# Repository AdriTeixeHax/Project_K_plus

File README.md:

# Project K+
DIY, Modular, Open Source Mechanical Keyboard and Macro-Pad with per-key RGB lighting.

## Features (keep in mind they are all optional or customizable):
- Per-key RGB lighting (because that's all that matters) using WS2812(B) 5050 SMD LEDs.
- RGB compatible mechanical switches.
- Modular design: detachable Macro-Pad, arrow keys, etc. With more room for expansion. Attachable via magnets placed all over the keyboard case.
- USB-C connectors for easy hot-swapping.
- Integrated 4-port USB 2.0 hub, with downstream USB-A and/or USB-C ports. If a USB-C port is connected, a USB-A port will be disconnected (on design process).
-

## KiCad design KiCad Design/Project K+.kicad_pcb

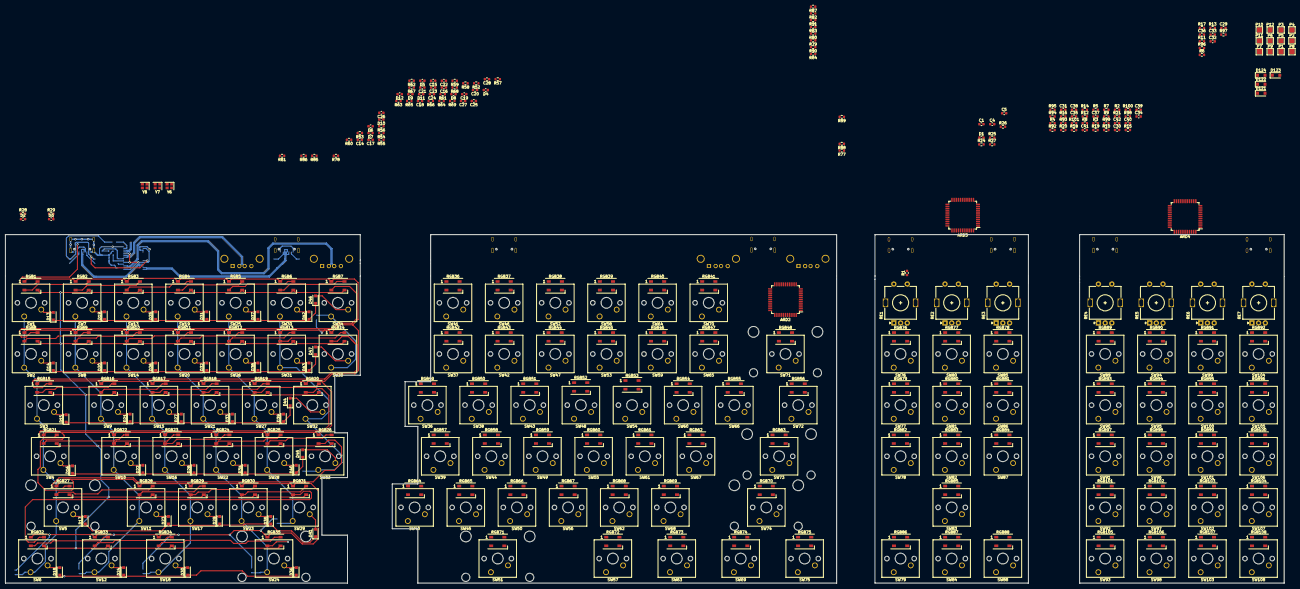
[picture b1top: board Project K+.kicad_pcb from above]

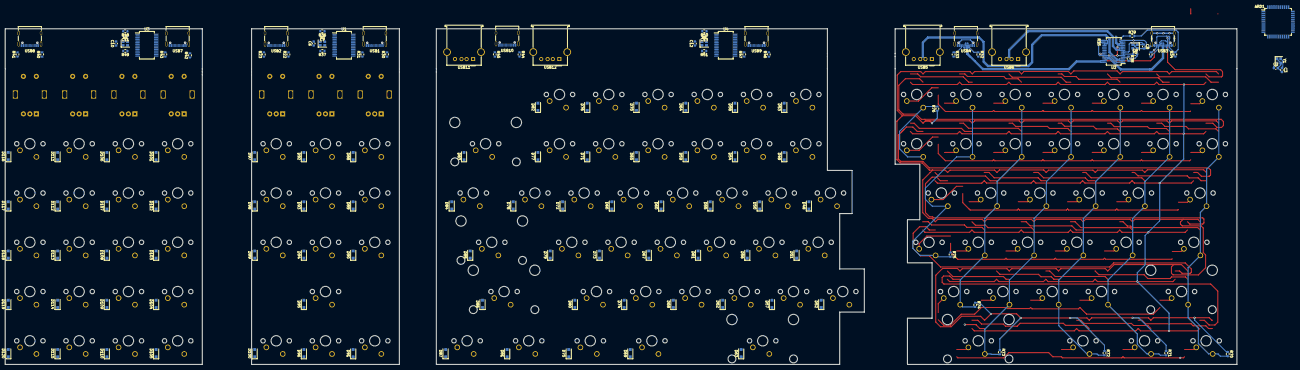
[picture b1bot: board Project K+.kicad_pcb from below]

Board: 2 copper layers, 476.2 x 129.8 mm, 530 parts (136 on the bottom side), 436 nets.

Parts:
ARD1, ARD2, ARD3, ARD4: ATmega32U4-A; TQFP-44_10x10mm_P0.8mm
C1, C5, C20, C21, C22, C23, C27, C28: 1uF; C_0603_1608Metric
C2, C3, C6, C7, C8, C9, C10, C11, C12, C13, C14, C15, C16, C17, C24, C25: 20pF; C_0603_1608Metric
C4, C18, C19, C26: 0.1uF; C_0603_1608Metric
C29, C30, C31, C32, C33, C34, C35, C36, C37, C38, C39, C40, C41, C42: 100n; C_0603_1608Metric
D1, D6, D8, D11: LED; C_0603_1608Metric
D2, D4, D5, D10: G; C_0603_1608Metric
D3, D7, D9, D12: Y; C_0603_1608Metric
D13, D14, D15, D16, D17, D18, D19, D20, D21, D22, D23, D24, D25, D26, D27, D28, D29, D30, D31, D32, D33, D34, D35, D36, D37, D38, D39, D40, D41, D42, D43, D44, D45, D46, D47, D48, D49, D50, D51, D52, D53, D54, D55, D56, D57, D58, D59, D60, D61, D62, D63, D64, D65, D66, D67, D68, D69, D70, D71, D72, D73, D74, D75, D76, D77, D78, D79, D80, D81, D82, D83, D84, D85, D86, D87, D88, D89, D90, D91, D92, D93, D94, D95, D96, D97, D98, D99, D100, D101, D102, D103, D104, D105, D106, D107, D108, D109, D110, D111, D112, D113, D114, D115, D116, D117, D118, D119, D120, D121, D122, D123, D124: D; D_SOD-123F
P1, P2, P3, P4, P5, P6, P7, P8, P9, P10, P11, P12: TESTPAD; TestPoint_Pad_2.0x2.0mm
R1, R10, R95: 220R; R_0603_1608Metric
R2, R3, R4, R5, R6, R7, R8, R9, R11, R12, R13, R14, R15, R16, R17, R18, R19, R20, R21, R25, R56, R57, R66, R70, R71, R72, R73, R74, R75, R76, R77, R78, R79, R80, R81, R82, R83, R84, R85, R86, R87, R88, R89, R90, R91, R92, R93, R94, R96, R97, R98, R99, R100, R101: 10K; R_0603_1608Metric
R22, R23, R32, R33, R40, R41, R44, R45: 5.1K; R_0603_1608Metric
R24, R60, R62, R68: 1K; R_0603_1608Metric
R26, R27, R52, R53, R54, R55, R64, R65: 22R; R_0603_1608Metric
R28, R29, R58, R59, R61, R63, R67, R69: 330R; R_0603_1608Metric
R30, R31, R34, R35, R42, R43, R46, R47: 56K; R_0603_1608Metric
R36, R37, R38, R39, R48, R49, R50, R51: 680R; R_0603_1608Metric
RE1, RE2, RE3, RE4, RE5, RE6, RE7: RotaryEncoder_Alps_EC11E-Switch_Vertical_H20mm
RGB1, RGB2, RGB3, RGB4, RGB5, RGB6, RGB7, RGB8, RGB9, RGB10, RGB11, RGB12, RGB13, RGB14, RGB15, RGB16, RGB17, RGB18, RGB19, RGB20, RGB21, RGB22, RGB23, RGB24, RGB25, RGB26, RGB27, RGB28, RGB29, RGB30, RGB31, RGB32, RGB33, RGB34, RGB35, RGB36, RGB37, RGB38, RGB39, RGB40, RGB41, RGB42, RGB43, RGB44, RGB45, RGB46, RGB47, RGB48, RGB49, RGB50, RGB51, RGB52, RGB53, RGB54, RGB55, RGB56, RGB57, RGB58, RGB59, RGB60, RGB61, RGB62, RGB63, RGB64, RGB65, RGB66, RGB67, RGB68, RGB69, RGB70, RGB71, RGB72, RGB73, RGB74, RGB75, RGB76, RGB77, RGB78, RGB79, RGB80, RGB81, RGB82, RGB83, RGB84, RGB85, RGB86, RGB87, RGB88, RGB89, RGB90, RGB91, RGB92, RGB93, RGB94, RGB95, RGB96, RGB97, RGB98, RGB99, RGB100, RGB101, RGB102, RGB103, RGB104, RGB105, RGB106, RGB107, RGB108: WS2812B; LED_WS2812B_PLCC4_5.0x5.0mm_P3.2mm
SW1: ESC; SW_Cherry_MX_1.00u_PCB
SW2: `; SW_Cherry_MX_1.00u_PCB
SW3: TAB; SW_Cherry_MX_1.50u_PCB
SW4: CAPS; SW_Cherry_MX_1.75u_PCB
SW5: L_SHIFT; SW_Cherry_MX_2.25u_PCB
SW6: L_CTRL; SW_Cherry_MX_1.25u_PCB
SW7: F1; SW_Cherry_MX_1.00u_PCB
SW8: 1; SW_Cherry_MX_1.00u_PCB
SW9: Q; SW_Cherry_MX_1.00u_PCB
SW10: A; SW_Cherry_MX_1.00u_PCB
SW11: Z; SW_Cherry_MX_1.00u_PCB
SW12: OS; SW_Cherry_MX_1.25u_PCB
SW13: F2; SW_Cherry_MX_1.00u_PCB
SW14: 2; SW_Cherry_MX_1.00u_PCB
SW15: W; SW_Cherry_MX_1.00u_PCB
SW16: S; SW_Cherry_MX_1.00u_PCB
SW17: X; SW_Cherry_MX_1.00u_PCB
SW18: L_ALT; SW_Cherry_MX_1.25u_PCB
SW19: F3; SW_Cherry_MX_1.00u_PCB
SW20: 3; SW_Cherry_MX_1.00u_PCB
SW21: E; SW_Cherry_MX_1.00u_PCB
SW22: D; SW_Cherry_MX_1.00u_PCB
SW23: C; SW_Cherry_MX_1.00u_PCB
SW24: L_SPACE; SW_Cherry_MX_2.25u_PCB
SW25: F4; SW_Cherry_MX_1.00u_PCB
SW26: 4; SW_Cherry_MX_1.00u_PCB
SW27: R; SW_Cherry_MX_1.00u_PCB
SW28: F; SW_Cherry_MX_1.00u_PCB
SW29: V; SW_Cherry_MX_1.00u_PCB
SW30: F5; SW_Cherry_MX_1.00u_PCB
SW31: 5; SW_Cherry_MX_1.00u_PCB
SW32: T; SW_Cherry_MX_1.00u_PCB
SW33: G; SW_Cherry_MX_1.00u_PCB
SW34: F6; SW_Cherry_MX_1.00u_PCB
SW35: 6; SW_Cherry_MX_1.00u_PCB
SW36: Y; SW_Cherry_MX_1.00u_PCB
SW37: 7; SW_Cherry_MX_1.00u_PCB
SW38: U; SW_Cherry_MX_1.00u_PCB
SW39: H; SW_Cherry_MX_1.00u_PCB
SW40: B; SW_Cherry_MX_1.00u_PCB
SW41: F7; SW_Cherry_MX_1.00u_PCB
SW42: 8; SW_Cherry_MX_1.00u_PCB
SW43: I; SW_Cherry_MX_1.00u_PCB
SW44: J; SW_Cherry_MX_1.00u_PCB
SW45: N; SW_Cherry_MX_1.00u_PCB
SW46: F8; SW_Cherry_MX_1.00u_PCB
SW47: 9; SW_Cherry_MX_1.00u_PCB
SW48: O; SW_Cherry_MX_1.00u_PCB
SW49: K; SW_Cherry_MX_1.00u_PCB
SW50: M; SW_Cherry_MX_1.00u_PCB
SW51: R_SPACE; SW_Cherry_MX_2.25u_PCB
SW52: F9; SW_Cherry_MX_1.00u_PCB
SW53: 0; SW_Cherry_MX_1.00u_PCB
SW54: P; SW_Cherry_MX_1.00u_PCB
SW55: L; SW_Cherry_MX_1.00u_PCB
SW56: ,; SW_Cherry_MX_1.00u_PCB
SW57: R_ALT; SW_Cherry_MX_1.25u_PCB
SW58: F10; SW_Cherry_MX_1.00u_PCB
SW59: -; SW_Cherry_MX_1.00u_PCB
SW60: [; SW_Cherry_MX_1.00u_PCB
SW61: ;; SW_Cherry_MX_1.00u_PCB
SW62: .; SW_Cherry_MX_1.00u_PCB
SW63: FN; SW_Cherry_MX_1.25u_PCB
SW64: F11; SW_Cherry_MX_1.00u_PCB
SW65: =; SW_Cherry_MX_1.00u_PCB
SW66: ]; SW_Cherry_MX_1.00u_PCB
SW67: '; SW_Cherry_MX_1.00u_PCB
SW68: /; SW_Cherry_MX_1.00u_PCB
SW69: MENU; SW_Cherry_MX_1.25u_PCB
SW70: F12; SW_Cherry_MX_1.00u_PCB
SW71: BACKSPACE; SW_Cherry_MX_2.00u_PCB
SW72: \; SW_Cherry_MX_1.50u_PCB
SW73: RETURN; SW_Cherry_MX_2.25u_PCB
SW74: R_SHIFT; SW_Cherry_MX_2.75u_PCB
SW75: R_CTRL; SW_Cherry_MX_1.25u_PCB
SW76: PRTSCR; SW_Cherry_MX_1.00u_PCB
SW77: INSERT; SW_Cherry_MX_1.00u_PCB
SW78: DELETE; SW_Cherry_MX_1.00u_PCB
SW79: LEFT; SW_Cherry_MX_1.00u_PCB
SW80: SCRLOCK; SW_Cherry_MX_1.00u_PCB
SW81: HOME; SW_Cherry_MX_1.00u_PCB
SW82: END; SW_Cherry_MX_1.00u_PCB
SW83: UP; SW_Cherry_MX_1.00u_PCB
SW84: DOWN; SW_Cherry_MX_1.00u_PCB
SW85: PAUSE; SW_Cherry_MX_1.00u_PCB
SW86: PGUP; SW_Cherry_MX_1.00u_PCB
SW87: PGDN; SW_Cherry_MX_1.00u_PCB
SW88: RIGHT; SW_Cherry_MX_1.00u_PCB
SW89: MACRO1; SW_Cherry_MX_1.00u_PCB
SW90: MACRO5; SW_Cherry_MX_1.00u_PCB
SW91: MACRO9; SW_Cherry_MX_1.00u_PCB
SW92: MACRO13; SW_Cherry_MX_1.00u_PCB
SW93: MACRO17; SW_Cherry_MX_1.00u_PCB
SW94: MACRO2; SW_Cherry_MX_1.00u_PCB
SW95: MACRO6; SW_Cherry_MX_1.00u_PCB
SW96: MACRO10; SW_Cherry_MX_1.00u_PCB
SW97: MACRO14; SW_Cherry_MX_1.00u_PCB
SW98: MACRO18; SW_Cherry_MX_1.00u_PCB
SW99: MACRO3; SW_Cherry_MX_1.00u_PCB
SW100: MACRO7; SW_Cherry_MX_1.00u_PCB
SW101: MACRO11; SW_Cherry_MX_1.00u_PCB
SW102: MACRO15; SW_Cherry_MX_1.00u_PCB
SW103: MACRO19; SW_Cherry_MX_1.00u_PCB
SW104: MACRO4; SW_Cherry_MX_1.00u_PCB
SW105: MACRO8; SW_Cherry_MX_1.00u_PCB
SW106: MACRO12; SW_Cherry_MX_1.00u_PCB
SW107: MACRO16; SW_Cherry_MX_1.00u_PCB
SW108: MACRO20; SW_Cherry_MX_1.00u_PCB
U1, U2, U3, U4: GL850G-HHGXX(SSOP-28); SSOP-28_5.3x10.2mm_P0.65mm
USB1, USB2, USB3, USB4, USB7, USB8, USB9, USB10: USB_C_Receptacle_USB2.0; USB_C_Receptacle_Palconn_UTC16-G
USB5, USB6, USB11, USB12: USB_A; USB_A_Molex_67643_Horizontal
Y1, Y6, Y7, Y8: 16MHz; Crystal_SMD_2520-4Pin_2.5x2.0mm
Y2, Y3, Y4, Y5: 12MHz; Crystal_SMD_2520-4Pin_2.5x2.0mm

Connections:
A1: ARD4.20 (PD2), C29.1, R6.1
A2: ARD4.25 (PD4), C37.1, R92.1
A3: ARD4.26 (PD6), C30.1, R7.1
A4: ARD3.21 (PD3), C38.1, R93.1
A5: ARD3.22 (PD5), C31.1, R8.1, R59.1
A6: ARD3.27 (PD7), C39.1, R94.1
A7: ARD3.41 (PF0), C32.1, R9.1
B1: ARD4.21 (PD3), C33.1, R11.1
B2: ARD4.22 (PD5), C40.1, R67.1, R96.1
B3: ARD4.27 (PD7), C34.1, R12.1
B4: ARD3.25 (PD4), C41.1, R97.1
B5: ARD3.26 (PD6), C35.1, R13.1
B6: ARD3.1 (PE6), C42.1, R98.1
B7: ARD3.40 (PF1), C36.1, R14.1
C0_A: ARD1.2 (UVCC), ARD1.7 (VBUS), ARD1.14 (VCC), ARD1.24 (AVCC), ARD1.34 (VCC), ARD1.44 (AVCC), ARD2.2 (UVCC), ARD2.7 (VBUS), ARD2.12 (PB7), ARD2.14 (VCC), ARD2.18 (PD0), ARD2.19 (PD1), ARD2.24 (AVCC), ARD2.28 (PB4), ARD2.29 (PB5), ARD2.30 (PB6), ARD2.31 (PC6), ARD2.32 (PC7), ARD2.34 (VCC), ARD2.44 (AVCC), ARD3.2 (UVCC), ARD3.7 (VBUS), ARD3.12 (PB7), ARD3.14 (VCC), ARD3.24 (AVCC), ARD3.28 (PB4), ARD3.29 (PB5), ARD3.30 (PB6), ARD3.34 (VCC), ARD3.44 (AVCC), ARD4.2 (UVCC), ARD4.7 (VBUS), ARD4.14 (VCC), ARD4.24 (AVCC), ARD4.28 (PB4), ARD4.29 (PB5), ARD4.30 (PB6), ARD4.34 (VCC), ARD4.44 (AVCC), C1.1, C22.1, C23.1, C28.1, D2.1 (K), D3.1 (K), R2.1, R3.1, R4.1, R5.1, R15.1, R16.1, R17.1, R18.1, R19.1, R20.1, R21.1, R24.1, R25.1, R30.2, R31.2, R34.2, R35.2, R37.2, R39.2, R42.2, R43.2, R46.2, R47.2, R49.2, R51.2, R56.1, R57.1, R60.1, R62.1, R66.1, R68.1, R77.1, R78.1, R79.1, R80.1, R81.1, R82.1, R83.1, R84.1, R85.1, R86.1, R87.1, R88.1, R89.1, R90.1, R91.1, R99.1, R100.1, R101.1, RGB1.1 (VDD), RGB2.1 (VDD), RGB3.1 (VDD), RGB4.1 (VDD), RGB5.1 (VDD), RGB6.1 (VDD), RGB7.1 (VDD), RGB8.1 (VDD), RGB9.1 (VDD), RGB10.1 (VDD), RGB11.1 (VDD), RGB12.1 (VDD), RGB13.1 (VDD), RGB14.1 (VDD), RGB15.1 (VDD), RGB16.1 (VDD), RGB17.1 (VDD), RGB18.1 (VDD), RGB19.1 (VDD), RGB20.1 (VDD), RGB21.1 (VDD), RGB22.1 (VDD), RGB23.1 (VDD), RGB24.1 (VDD), RGB25.1 (VDD), RGB26.1 (VDD), RGB27.1 (VDD), RGB28.1 (VDD), RGB29.1 (VDD), RGB30.1 (VDD), RGB31.1 (VDD), RGB32.1 (VDD), RGB33.1 (VDD), RGB34.1 (VDD), RGB35.1 (VDD), RGB36.1 (VDD), RGB37.1 (VDD), RGB38.1 (VDD), RGB39.1 (VDD), RGB40.1 (VDD), RGB41.1 (VDD), RGB42.1 (VDD), RGB43.1 (VDD), RGB44.1 (VDD), RGB45.1 (VDD), RGB46.1 (VDD), RGB47.1 (VDD), RGB48.1 (VDD), RGB49.1 (VDD), RGB50.1 (VDD), RGB51.1 (VDD), RGB52.1 (VDD), RGB53.1 (VDD), RGB54.1 (VDD), RGB55.1 (VDD), RGB56.1 (VDD), RGB57.1 (VDD), RGB58.1 (VDD), RGB59.1 (VDD), RGB60.1 (VDD), RGB61.1 (VDD), RGB62.1 (VDD), RGB63.1 (VDD), RGB64.1 (VDD), RGB65.1 (VDD), RGB66.1 (VDD), RGB67.1 (VDD), RGB68.1 (VDD), RGB69.1 (VDD), RGB70.1 (VDD), RGB71.1 (VDD), RGB72.1 (VDD), RGB73.1 (VDD), RGB74.1 (VDD), RGB75.1 (VDD), RGB76.1 (VDD), RGB77.1 (VDD), RGB78.1 (VDD), RGB79.1 (VDD), RGB80.1 (VDD), RGB81.1 (VDD), RGB82.1 (VDD), RGB83.1 (VDD), RGB84.1 (VDD), RGB85.1 (VDD), RGB86.1 (VDD), RGB87.1 (VDD), RGB88.1 (VDD), RGB89.1 (VDD), RGB90.1 (VDD), RGB91.1 (VDD), RGB92.1 (VDD), RGB93.1 (VDD), RGB94.1 (VDD), RGB95.1 (VDD), RGB96.1 (VDD), RGB97.1 (VDD), RGB98.1 (VDD), RGB99.1 (VDD), RGB100.1 (VDD), RGB101.1 (VDD), RGB102.1 (VDD), RGB103.1 (VDD), RGB104.1 (VDD), RGB105.1 (VDD), RGB106.1 (VDD), RGB107.1 (VDD), RGB108.1 (VDD), U1.23 (V5), U2.23 (V5), U3.23 (V5), U4.23 (V5), USB1.A4 (VBUS), USB1.A9 (VBUS), USB1.B4 (VBUS), USB1.B9 (VBUS), USB2.A4 (VBUS), USB2.A9 (VBUS), USB2.B4 (VBUS), USB2.B9 (VBUS), USB3.A4 (VBUS), USB3.A9 (VBUS), USB3.B4 (VBUS), USB3.B9 (VBUS), USB4.A4 (VBUS), USB4.A9 (VBUS), USB4.B4 (VBUS), USB4.B9 (VBUS), USB5.1 (VBUS), USB6.1 (VBUS), USB7.A4 (VBUS), USB7.A9 (VBUS), USB7.B4 (VBUS), USB7.B9 (VBUS), USB8.A4 (VBUS), USB8.A9 (VBUS), USB8.B4 (VBUS), USB8.B9 (VBUS), USB9.A4 (VBUS), USB9.A9 (VBUS), USB9.B4 (VBUS), USB9.B9 (VBUS), USB10.A4 (VBUS), USB10.A9 (VBUS), USB10.B4 (VBUS), USB10.B9 (VBUS), USB11.1 (VBUS), USB12.1 (VBUS)
C0_L: ARD1.18 (PD0), R70.1
C1_L: ARD1.19 (PD1), R71.1
C2_L: ARD1.20 (PD2), R72.1
C3_L: ARD1.21 (PD3), R73.1
C4_L: ARD1.25 (PD4), R74.1
C5_L: ARD1.26 (PD6), R75.1
C6_L: ARD1.27 (PD7), R76.1
D+_A: R64.2, U1.12 (DP4)
D+_N: R54.2, U3.12 (DP4)
D+_R: R52.2, U4.12 (DP4)
D-_A: R65.1, U1.11 (DM4)
D-_N: R55.1, U3.11 (DM4)
D-_R: R53.1, U4.11 (DM4)
GND: ARD1.5 (UGND), ARD1.15 (GND), ARD1.23 (GND), ARD1.33 (~HWB~/PE2), ARD1.35 (GND), ARD1.43 (GND), ARD2.5 (UGND), ARD2.15 (GND), ARD2.23 (GND), ARD2.33 (~HWB~/PE2), ARD2.35 (GND), ARD2.43 (GND), ARD3.5 (UGND), ARD3.15 (GND), ARD3.23 (GND), ARD3.33 (~HWB~/PE2), ARD3.35 (GND), ARD3.43 (GND), ARD4.5 (UGND), ARD4.15 (GND), ARD4.23 (GND), ARD4.33 (~HWB~/PE2), ARD4.35 (GND), ARD4.43 (GND), C1.2, C2.2, C3.2, C4.2, C5.2, C6.2, C7.2, C8.2, C9.2, C10.2, C11.2, C12.2, C13.2, C14.2, C15.2, C16.2, C17.2, C18.2, C19.2, C20.2, C21.2, C22.2, C23.2, C24.2, C25.2, C26.2, C27.2, C28.2, C29.2, C30.2, C31.2, C32.2, C33.2, C34.2, C35.2, C36.2, C37.2, C38.2, C39.2, C40.2, C41.2, C42.2, D1.1 (K), D6.1 (K), D8.1 (K), D11.1 (K), R22.2, R23.2, R32.2, R33.2, R36.2, R38.2, R40.2, R41.2, R44.2, R45.2, R48.2, R50.2, RE1.C, RE1.S2, RE2.C, RE2.S2, RE3.C, RE4.C, RE5.C, RE5.S2, RE6.C, RE7.C, RGB1.3 (VSS), RGB2.3 (VSS), RGB3.3 (VSS), RGB4.3 (VSS), RGB5.3 (VSS), RGB6.3 (VSS), RGB7.3 (VSS), RGB8.3 (VSS), RGB9.3 (VSS), RGB10.3 (VSS), RGB11.3 (VSS), RGB12.3 (VSS), RGB13.3 (VSS), RGB14.3 (VSS), RGB15.3 (VSS), RGB16.3 (VSS), RGB17.3 (VSS), RGB18.3 (VSS), RGB19.3 (VSS), RGB20.3 (VSS), RGB21.3 (VSS), RGB22.3 (VSS), RGB23.3 (VSS), RGB24.3 (VSS), RGB25.3 (VSS), RGB26.3 (VSS), RGB27.3 (VSS), RGB28.3 (VSS), RGB29.3 (VSS), RGB30.3 (VSS), RGB31.3 (VSS), RGB32.3 (VSS), RGB33.3 (VSS), RGB34.3 (VSS), RGB35.3 (VSS), RGB36.3 (VSS), RGB37.3 (VSS), RGB38.3 (VSS), RGB39.3 (VSS), RGB40.3 (VSS), RGB41.3 (VSS), RGB42.3 (VSS), RGB43.3 (VSS), RGB44.3 (VSS), RGB45.3 (VSS), RGB46.3 (VSS), RGB47.3 (VSS), RGB48.3 (VSS), RGB49.3 (VSS), RGB50.3 (VSS), RGB51.3 (VSS), RGB52.3 (VSS), RGB53.3 (VSS), RGB54.3 (VSS), RGB55.3 (VSS), RGB56.3 (VSS), RGB57.3 (VSS), RGB58.3 (VSS), RGB59.3 (VSS), RGB60.3 (VSS), RGB61.3 (VSS), RGB62.3 (VSS), RGB63.3 (VSS), RGB64.3 (VSS), RGB65.3 (VSS), RGB66.3 (VSS), RGB67.3 (VSS), RGB68.3 (VSS), RGB69.3 (VSS), RGB70.3 (VSS), RGB71.3 (VSS), RGB72.3 (VSS), RGB73.3 (VSS), RGB74.3 (VSS), RGB75.3 (VSS), RGB76.3 (VSS), RGB77.3 (VSS), RGB78.3 (VSS), RGB79.3 (VSS), RGB80.3 (VSS), RGB81.3 (VSS), RGB82.3 (VSS), RGB83.3 (VSS), RGB84.3 (VSS), RGB85.3 (VSS), RGB86.3 (VSS), RGB87.3 (VSS), RGB88.3 (VSS), RGB89.3 (VSS), RGB90.3 (VSS), RGB91.3 (VSS), RGB92.3 (VSS), RGB93.3 (VSS), RGB94.3 (VSS), RGB95.3 (VSS), RGB96.3 (VSS), RGB97.3 (VSS), RGB98.3 (VSS), RGB99.3 (VSS), RGB100.3 (VSS), RGB101.3 (VSS), RGB102.3 (VSS), RGB103.3 (VSS), RGB104.3 (VSS), RGB105.3 (VSS), RGB106.3 (VSS), RGB107.3 (VSS), RGB108.3 (VSS), U1.14 (TEST/SCL), U1.15 (GND), U1.17 (PSELF), U1.18 (PGANG), U2.14 (TEST/SCL), U2.15 (GND), U2.17 (PSELF), U2.18 (PGANG), U3.14 (TEST/SCL), U3.15 (GND), U3.17 (PSELF), U3.18 (PGANG), U4.14 (TEST/SCL), U4.15 (GND), U4.17 (PSELF), U4.18 (PGANG), USB1.A1 (GND), USB1.A12 (GND), USB1.B1 (GND), USB1.B12 (GND), USB1.S1 (SHIELD), USB2.A1 (GND), USB2.A12 (GND), USB2.B1 (GND), USB2.B12 (GND), USB2.S1 (SHIELD), USB3.A1 (GND), USB3.A12 (GND), USB3.B1 (GND), USB3.B12 (GND), USB3.S1 (SHIELD), USB4.A1 (GND), USB4.A12 (GND), USB4.B1 (GND), USB4.B12 (GND), USB4.S1 (SHIELD), USB5.4 (GND), USB5.5 (Shield), USB6.4 (GND), USB6.5 (Shield), USB7.A1 (GND), USB7.A12 (GND), USB7.B1 (GND), USB7.B12 (GND), USB7.S1 (SHIELD), USB8.A1 (GND), USB8.A12 (GND), USB8.B1 (GND), USB8.B12 (GND), USB8.S1 (SHIELD), USB9.A1 (GND), USB9.A12 (GND), USB9.B1 (GND), USB9.B12 (GND), USB9.S1 (SHIELD), USB10.A1 (GND), USB10.A12 (GND), USB10.B1 (GND), USB10.B12 (GND), USB10.S1 (SHIELD), USB11.4 (GND), USB11.5 (Shield), USB12.4 (GND), USB12.5 (Shield), Y1.1, Y1.3, Y2.2, Y2.4, Y3.2, Y3.4, Y4.2, Y4.4, Y5.2, Y5.4, Y6.1, Y6.3, Y7.1, Y7.3, Y8.1, Y8.3
LEFT1 D+: U2.26 (DP0), USB3.A6 (D+), USB3.B6 (D+)
LEFT1 D-: U2.25 (DM0), USB3.A7 (D-), USB3.B7 (D-)
LEFT2 D+: U2.28 (DP1), USB4.A6 (D+), USB4.B6 (D+)
LEFT2 D-: U2.27 (DM1), USB4.A7 (D-), USB4.B7 (D-)
LEFT3 D+: U2.3 (DP2), USB5.3 (D+)
LEFT3 D-: U2.2 (DM2), USB5.2 (D-)
LEFT4 D+: U2.9 (DP3), USB6.3 (D+)
LEFT4 D-: U2.8 (DM3), USB6.2 (D-)
L_D+: R26.2, U2.12 (DP4)
L_D-: R27.1, U2.11 (DM4)
unnamed: ARD1.3 (D-), R27.2
unnamed: ARD1.4 (D+), R26.1
unnamed: ARD1.6 (UCAP), C5.1
unnamed: ARD1.8 (PB0), R29.1
unnamed: ARD1.9 (PB1), P1.1 (Pad)
unnamed: ARD1.10 (PB2), P2.1 (Pad)
unnamed: ARD1.11 (PB3), P3.1 (Pad)
unnamed: ARD1.13 (~RESET), R25.2
unnamed: ARD1.16 (XTAL2), C3.1, Y1.4
unnamed: ARD1.17 (XTAL1), C2.1, Y1.2
unnamed: ARD1.22 (PD5), R28.1
unnamed: ARD1.42 (AREF), C4.1
unnamed: ARD2.3 (D-), R53.2
unnamed: ARD2.4 (D+), R52.1
unnamed: ARD2.6 (UCAP), C20.1
unnamed: ARD2.8 (PB0), R61.1
unnamed: ARD2.9 (PB1), P4.1 (Pad)
unnamed: ARD2.10 (PB2), P5.1 (Pad)
unnamed: ARD2.11 (PB3), P6.1 (Pad)
unnamed: ARD2.13 (~RESET), R56.2
unnamed: ARD2.16 (XTAL2), C16.1, Y6.4
unnamed: ARD2.17 (XTAL1), C14.1, Y6.2
unnamed: ARD2.22 (PD5), R58.1
unnamed: ARD2.42 (AREF), C18.1
unnamed: ARD3.3 (D-), R55.2
unnamed: ARD3.4 (D+), R54.1
unnamed: ARD3.6 (UCAP), C21.1
unnamed: ARD3.8 (PB0), R63.1
unnamed: ARD3.9 (PB1), P7.1 (Pad)
unnamed: ARD3.10 (PB2), P8.1 (Pad)
unnamed: ARD3.11 (PB3), P9.1 (Pad)
unnamed: ARD3.13 (~RESET), R57.2
unnamed: ARD3.16 (XTAL2), C17.1, Y7.4
unnamed: ARD3.17 (XTAL1), C15.1, Y7.2
unnamed: ARD3.42 (AREF), C19.1
unnamed: ARD4.3 (D-), R65.2
unnamed: ARD4.4 (D+), R64.1
unnamed: ARD4.6 (UCAP), C27.1
unnamed: ARD4.8 (PB0), R69.1
unnamed: ARD4.9 (PB1), P10.1 (Pad)
unnamed: ARD4.10 (PB2), P11.1 (Pad)
unnamed: ARD4.11 (PB3), P12.1 (Pad)
unnamed: ARD4.13 (~RESET), R66.2
unnamed: ARD4.16 (XTAL2), C25.1, Y8.4
unnamed: ARD4.17 (XTAL1), C24.1, Y8.2
unnamed: ARD4.42 (AREF), C26.1
unnamed: C6.1, U1.7 (X2), Y2.1
unnamed: C7.1, U1.6 (X1), Y2.3
unnamed: C8.1, U2.7 (X2), Y3.1
unnamed: C9.1, U2.6 (X1), Y3.3
unnamed: C10.1, U3.7 (X2), Y4.1
unnamed: C11.1, U3.6 (X1), Y4.3
unnamed: C12.1, U4.7 (X2), Y5.1
unnamed: C13.1, U4.6 (X1), Y5.3
unnamed: D1.2 (A), R24.2
unnamed: D2.2 (A), R28.2
unnamed: D4.2 (A), R58.2
unnamed: D5.2 (A), R59.2
unnamed: D6.2 (A), R60.2
unnamed: D7.2 (A), R61.2
unnamed: D8.2 (A), R62.2
unnamed: D9.2 (A), R63.2
unnamed: D10.2 (A), R67.2
unnamed: D11.2 (A), R68.2
unnamed: D12.2 (A), R69.2
unnamed: D13.2 (A), SW1.2
unnamed: D14.2 (A), SW2.2
unnamed: D15.2 (A), SW3.2
unnamed: D16.2 (A), SW4.2
unnamed: D17.2 (A), SW5.2
unnamed: D18.2 (A), SW6.2
unnamed: D19.2 (A), SW7.2
unnamed: D20.2 (A), SW8.2
unnamed: D21.2 (A), SW9.2
unnamed: D22.2 (A), SW10.2
unnamed: D23.2 (A), SW11.2
unnamed: D24.2 (A), SW12.2
unnamed: D25.2 (A), SW13.2
unnamed: D26.2 (A), SW14.2
unnamed: D27.2 (A), SW15.2
unnamed: D28.2 (A), SW16.2
unnamed: D29.2 (A), SW17.2
unnamed: D30.2 (A), SW18.2
unnamed: D31.2 (A), SW19.2
unnamed: D32.2 (A), SW20.2
unnamed: D33.2 (A), SW21.2
unnamed: D34.2 (A), SW22.2
unnamed: D35.2 (A), SW23.2
unnamed: D36.2 (A), SW24.2
unnamed: D37.2 (A), SW25.2
unnamed: D38.2 (A), SW26.2
unnamed: D39.2 (A), SW27.2
unnamed: D40.2 (A), SW28.2
unnamed: D41.2 (A), SW29.2
unnamed: D42.2 (A), SW30.2
unnamed: D43.2 (A), SW31.2
unnamed: D44.2 (A), SW32.2
unnamed: D45.2 (A), SW33.2
unnamed: D46.2 (A), SW34.2
unnamed: D47.2 (A), SW35.2
unnamed: D48.2 (A), SW36.2
unnamed: D49.2 (A), SW37.2
unnamed: D50.2 (A), SW38.2
unnamed: D51.2 (A), SW39.2
unnamed: D52.2 (A), SW40.2
unnamed: D53.2 (A), SW41.2
unnamed: D54.2 (A), SW42.2
unnamed: D55.2 (A), SW43.2
unnamed: D56.2 (A), SW44.2
unnamed: D57.2 (A), SW45.2
unnamed: D58.2 (A), SW46.2
unnamed: D59.2 (A), SW47.2
unnamed: D60.2 (A), SW48.2
unnamed: D61.2 (A), SW49.2
unnamed: D62.2 (A), SW50.2
unnamed: D63.2 (A), SW51.2
unnamed: D64.2 (A), SW52.2
unnamed: D65.2 (A), SW53.2
unnamed: D66.2 (A), SW54.2
unnamed: D67.2 (A), SW55.2
unnamed: D68.2 (A), SW56.2
unnamed: D69.2 (A), SW57.2
unnamed: D70.2 (A), SW58.2
unnamed: D71.2 (A), SW59.2
unnamed: D72.2 (A), SW60.2
unnamed: D73.2 (A), SW61.2
unnamed: D74.2 (A), SW62.2
unnamed: D75.2 (A), SW63.2
unnamed: D76.2 (A), SW64.2
unnamed: D77.2 (A), SW65.2
unnamed: D78.2 (A), SW66.2
unnamed: D79.2 (A), SW67.2
unnamed: D80.2 (A), SW68.2
unnamed: D81.2 (A), SW69.2
unnamed: D82.2 (A), SW70.2
unnamed: D83.2 (A), SW71.2
unnamed: D84.2 (A), SW72.2
unnamed: D85.2 (A), SW73.2
unnamed: D86.2 (A), SW74.2
unnamed: D87.2 (A), SW75.2
unnamed: D88.2 (A), SW76.2
unnamed: D89.2 (A), SW77.2
unnamed: D90.2 (A), SW78.2
unnamed: D91.2 (A), SW79.2
unnamed: D92.2 (A), SW80.2
unnamed: D93.2 (A), SW81.2
unnamed: D94.2 (A), SW82.2
unnamed: D95.2 (A), SW83.2
unnamed: D96.2 (A), SW84.2
unnamed: D97.2 (A), SW85.2
unnamed: D98.2 (A), SW86.2
unnamed: D99.2 (A), SW87.2
unnamed: D100.2 (A), SW88.2
unnamed: D101.2 (A), SW89.2
unnamed: D102.2 (A), SW90.2
unnamed: D103.2 (A), SW91.2
unnamed: D104.2 (A), SW92.2
unnamed: D105.2 (A), SW93.2
unnamed: D106.2 (A), SW94.2
unnamed: D107.2 (A), SW95.2
unnamed: D108.2 (A), SW96.2
unnamed: D109.2 (A), SW97.2
unnamed: D110.2 (A), SW98.2
unnamed: D111.2 (A), SW99.2
unnamed: D112.2 (A), SW100.2
unnamed: D113.2 (A), SW101.2
unnamed: D114.2 (A), SW102.2
unnamed: D115.2 (A), SW103.2
unnamed: D116.2 (A), SW104.2
unnamed: D117.2 (A), SW105.2
unnamed: D118.2 (A), SW106.2
unnamed: D119.2 (A), SW107.2
unnamed: D120.2 (A), SW108.2
unnamed: R1.2, RE1.S1
unnamed: R3.2, R7.2, RE2.A
unnamed: R4.2, R8.2, RE3.A
unnamed: R5.2, R9.2, RE4.A
unnamed: R10.2, RE2.S1
unnamed: R12.2, R16.2, RE2.B
unnamed: R13.2, R17.2, RE3.B
unnamed: R14.2, R18.2, RE4.B
unnamed: R19.2, R92.2, RE5.A
unnamed: R20.2, R93.2, RE6.A
unnamed: R21.2, R94.2, RE7.A
unnamed: R22.1, USB2.A5 (CC1)
unnamed: R23.1, USB2.B5 (CC2)
unnamed: D3.2 (A), R29.2
unnamed: R30.1, USB1.A5 (CC1)
unnamed: R31.1, USB1.B5 (CC2)
unnamed: R32.1, USB4.A5 (CC1)
unnamed: R33.1, USB4.B5 (CC2)
unnamed: R34.1, USB3.A5 (CC1)
unnamed: R35.1, USB3.B5 (CC2)
unnamed: R36.1, U1.4 (RREF)
unnamed: R37.1, U1.13 (#RESET)
unnamed: R38.1, U2.4 (RREF)
unnamed: R39.1, U2.13 (#RESET)
unnamed: R40.1, USB8.A5 (CC1)
unnamed: R41.1, USB8.B5 (CC2)
unnamed: R42.1, USB7.A5 (CC1)
unnamed: R43.1, USB7.B5 (CC2)
unnamed: R44.1, USB10.A5 (CC1)
unnamed: R45.1, USB10.B5 (CC2)
unnamed: R46.1, USB9.A5 (CC1)
unnamed: R47.1, USB9.B5 (CC2)
unnamed: R48.1, U3.4 (RREF)
unnamed: R49.1, U3.13 (#RESET)
unnamed: R50.1, U4.4 (RREF)
unnamed: R51.1, U4.13 (#RESET)
unnamed: R70.2, SW1.1, SW2.1, SW3.1, SW4.1, SW5.1, SW6.1
unnamed: R71.2, SW7.1, SW8.1, SW9.1, SW10.1, SW11.1, SW12.1
unnamed: R72.2, SW13.1, SW14.1, SW15.1, SW16.1, SW17.1, SW18.1
unnamed: R73.2, SW19.1, SW20.1, SW21.1, SW22.1, SW23.1, SW24.1
unnamed: R74.2, SW25.1, SW26.1, SW27.1, SW28.1, SW29.1
unnamed: R75.2, SW30.1, SW31.1, SW32.1, SW33.1
unnamed: R76.2, SW34.1, SW35.1
unnamed: R77.2, SW36.1
unnamed: R78.2, SW37.1, SW38.1, SW39.1, SW40.1
unnamed: R79.2, SW41.1, SW42.1, SW43.1, SW44.1, SW45.1
unnamed: R80.2, SW46.1, SW47.1, SW48.1, SW49.1, SW50.1, SW51.1
unnamed: R81.2, SW52.1, SW53.1, SW54.1, SW55.1, SW56.1, SW57.1
unnamed: R82.2, SW58.1, SW59.1, SW60.1, SW61.1, SW62.1, SW63.1
unnamed: R83.2, SW64.1, SW65.1, SW66.1, SW67.1, SW68.1, SW69.1
unnamed: R84.2, SW70.1, SW71.1, SW72.1, SW73.1, SW74.1, SW75.1
unnamed: R85.2, SW76.1, SW77.1, SW78.1, SW79.1
unnamed: R86.2, SW80.1, SW81.1, SW82.1, SW83.1, SW84.1
unnamed: R87.2, SW85.1, SW86.1, SW87.1, SW88.1
unnamed: R95.2, RE5.S1
unnamed: R96.2, R99.2, RE5.B
unnamed: R97.2, R100.2, RE6.B
unnamed: R98.2, R101.2, RE7.B
unnamed: R2.2, R6.2, RE1.A
unnamed: R11.2, R15.2, RE1.B
unnamed: RGB1.2 (DOUT), RGB2.4 (DIN)
unnamed: RGB2.2 (DOUT), RGB3.4 (DIN)
unnamed: RGB3.2 (DOUT), RGB4.4 (DIN)
unnamed: RGB4.2 (DOUT), RGB5.4 (DIN)
unnamed: RGB5.2 (DOUT), RGB6.4 (DIN)
unnamed: RGB6.2 (DOUT), RGB7.4 (DIN)
unnamed: RGB7.2 (DOUT), RGB8.4 (DIN)
unnamed: RGB8.2 (DOUT), RGB9.4 (DIN)
unnamed: RGB10.2 (DOUT), RGB11.4 (DIN)
unnamed: RGB9.2 (DOUT), RGB10.4 (DIN)
unnamed: RGB11.2 (DOUT), RGB12.4 (DIN)
unnamed: RGB12.2 (DOUT), RGB13.4 (DIN)
unnamed: RGB13.2 (DOUT), RGB14.4 (DIN)
unnamed: RGB14.2 (DOUT), RGB15.4 (DIN)
unnamed: RGB15.2 (DOUT), RGB16.4 (DIN)
unnamed: RGB16.2 (DOUT), RGB17.4 (DIN)
unnamed: RGB17.2 (DOUT), RGB18.4 (DIN)
unnamed: RGB18.2 (DOUT), RGB19.4 (DIN)
unnamed: RGB19.2 (DOUT), RGB20.4 (DIN)
unnamed: RGB20.2 (DOUT), RGB21.4 (DIN)
unnamed: RGB21.2 (DOUT), RGB22.4 (DIN)
unnamed: RGB22.2 (DOUT), RGB23.4 (DIN)
unnamed: RGB23.2 (DOUT), RGB24.4 (DIN)
unnamed: RGB24.2 (DOUT), RGB25.4 (DIN)
unnamed: RGB25.2 (DOUT), RGB26.4 (DIN)
unnamed: RGB26.2 (DOUT), RGB27.4 (DIN)
unnamed: RGB27.2 (DOUT), RGB28.4 (DIN)
unnamed: RGB28.2 (DOUT), RGB29.4 (DIN)
unnamed: RGB29.2 (DOUT), RGB30.4 (DIN)
unnamed: RGB30.2 (DOUT), RGB31.4 (DIN)
unnamed: RGB31.2 (DOUT), RGB32.4 (DIN)
unnamed: RGB32.2 (DOUT), RGB33.4 (DIN)
unnamed: RGB33.2 (DOUT), RGB34.4 (DIN)
unnamed: RGB34.2 (DOUT), RGB35.4 (DIN)
unnamed: RGB36.2 (DOUT), RGB37.4 (DIN)
unnamed: RGB37.2 (DOUT), RGB38.4 (DIN)
unnamed: RGB38.2 (DOUT), RGB39.4 (DIN)
unnamed: RGB39.2 (DOUT), RGB40.4 (DIN)
unnamed: RGB40.2 (DOUT), RGB41.4 (DIN)
unnamed: RGB41.2 (DOUT), RGB42.4 (DIN)
unnamed: RGB42.2 (DOUT), RGB43.4 (DIN)
unnamed: RGB43.2 (DOUT), RGB44.4 (DIN)
unnamed: RGB44.2 (DOUT), RGB45.4 (DIN)
unnamed: RGB45.2 (DOUT), RGB46.4 (DIN)
unnamed: RGB46.2 (DOUT), RGB47.4 (DIN)
unnamed: RGB47.2 (DOUT), RGB48.4 (DIN)
unnamed: RGB48.2 (DOUT), RGB49.4 (DIN)
unnamed: RGB49.2 (DOUT), RGB50.4 (DIN)
unnamed: RGB50.2 (DOUT), RGB51.4 (DIN)
unnamed: RGB51.2 (DOUT), RGB52.4 (DIN)
unnamed: RGB52.2 (DOUT), RGB53.4 (DIN)
unnamed: RGB53.2 (DOUT), RGB54.4 (DIN)
unnamed: RGB54.2 (DOUT), RGB55.4 (DIN)
unnamed: RGB55.2 (DOUT), RGB56.4 (DIN)
unnamed: RGB56.2 (DOUT), RGB57.4 (DIN)
unnamed: RGB57.2 (DOUT), RGB58.4 (DIN)
unnamed: RGB58.2 (DOUT), RGB59.4 (DIN)
unnamed: RGB59.2 (DOUT), RGB60.4 (DIN)
unnamed: RGB60.2 (DOUT), RGB61.4 (DIN)
unnamed: RGB61.2 (DOUT), RGB62.4 (DIN)
unnamed: RGB62.2 (DOUT), RGB63.4 (DIN)
unnamed: RGB63.2 (DOUT), RGB64.4 (DIN)
unnamed: RGB64.2 (DOUT), RGB65.4 (DIN)
unnamed: RGB65.2 (DOUT), RGB66.4 (DIN)
unnamed: RGB66.2 (DOUT), RGB67.4 (DIN)
unnamed: RGB67.2 (DOUT), RGB68.4 (DIN)
unnamed: RGB68.2 (DOUT), RGB69.4 (DIN)
unnamed: RGB69.2 (DOUT), RGB70.4 (DIN)
unnamed: RGB70.2 (DOUT), RGB71.4 (DIN)
unnamed: RGB71.2 (DOUT), RGB72.4 (DIN)
unnamed: RGB72.2 (DOUT), RGB73.4 (DIN)
unnamed: RGB73.2 (DOUT), RGB74.4 (DIN)
unnamed: RGB74.2 (DOUT), RGB75.4 (DIN)
unnamed: RGB76.2 (DOUT), RGB77.4 (DIN)
unnamed: RGB77.2 (DOUT), RGB78.4 (DIN)
unnamed: RGB78.2 (DOUT), RGB79.4 (DIN)
unnamed: RGB79.2 (DOUT), RGB80.4 (DIN)
unnamed: RGB80.2 (DOUT), RGB81.4 (DIN)
unnamed: RGB81.2 (DOUT), RGB82.4 (DIN)
unnamed: RGB82.2 (DOUT), RGB83.4 (DIN)
unnamed: RGB83.2 (DOUT), RGB84.4 (DIN)
unnamed: RGB84.2 (DOUT), RGB85.4 (DIN)
unnamed: RGB85.2 (DOUT), RGB86.4 (DIN)
unnamed: RGB86.2 (DOUT), RGB87.4 (DIN)
unnamed: RGB87.2 (DOUT), RGB88.4 (DIN)
unnamed: RGB89.2 (DOUT), RGB90.4 (DIN)
unnamed: RGB90.2 (DOUT), RGB91.4 (DIN)
unnamed: RGB91.2 (DOUT), RGB92.4 (DIN)
unnamed: RGB92.2 (DOUT), RGB93.4 (DIN)
unnamed: RGB93.2 (DOUT), RGB94.4 (DIN)
unnamed: RGB94.2 (DOUT), RGB95.4 (DIN)
unnamed: RGB95.2 (DOUT), RGB96.4 (DIN)
unnamed: RGB96.2 (DOUT), RGB97.4 (DIN)
unnamed: RGB97.2 (DOUT), RGB98.4 (DIN)
unnamed: RGB98.2 (DOUT), RGB99.4 (DIN)
unnamed: RGB100.2 (DOUT), RGB101.4 (DIN)
unnamed: RGB99.2 (DOUT), RGB100.4 (DIN)
unnamed: RGB101.2 (DOUT), RGB102.4 (DIN)
unnamed: RGB102.2 (DOUT), RGB103.4 (DIN)
unnamed: RGB103.2 (DOUT), RGB104.4 (DIN)
unnamed: RGB104.2 (DOUT), RGB105.4 (DIN)
unnamed: RGB105.2 (DOUT), RGB106.4 (DIN)
unnamed: RGB106.2 (DOUT), RGB107.4 (DIN)
unnamed: RGB107.2 (DOUT), RGB108.4 (DIN)
unnamed: U1.1 (AVDD), U1.5 (AVDD), U1.10 (AVDD), U1.16 (DVDD), U1.24 (V33)
unnamed: U1.25 (DM0), USB1.A7 (D-), USB1.B7 (D-)
unnamed: U1.26 (DP0), USB1.A6 (D+), USB1.B6 (D+)
unnamed: U1.27 (DM1), USB2.A7 (D-), USB2.B7 (D-)
unnamed: U1.28 (DP1), USB2.A6 (D+), USB2.B6 (D+)
unnamed: U2.1 (AVDD), U2.5 (AVDD), U2.10 (AVDD), U2.16 (DVDD), U2.24 (V33)
unnamed: U3.1 (AVDD), U3.5 (AVDD), U3.10 (AVDD), U3.16 (DVDD), U3.24 (V33)
unnamed: U3.25 (DM0), USB7.A7 (D-), USB7.B7 (D-)
unnamed: U3.26 (DP0), USB7.A6 (D+), USB7.B6 (D+)
unnamed: U3.27 (DM1), USB8.A7 (D-), USB8.B7 (D-)
unnamed: U3.28 (DP1), USB8.A6 (D+), USB8.B6 (D+)
unnamed: U4.1 (AVDD), U4.5 (AVDD), U4.10 (AVDD), U4.16 (DVDD), U4.24 (V33)
unnamed: U4.2 (DM2), USB11.2 (D-)
unnamed: U4.3 (DP2), USB11.3 (D+)
unnamed: U4.8 (DM3), USB12.2 (D-)
unnamed: U4.9 (DP3), USB12.3 (D+)
unnamed: U4.25 (DM0), USB9.A7 (D-), USB9.B7 (D-)
unnamed: U4.26 (DP0), USB9.A6 (D+), USB9.B6 (D+)
unnamed: U4.27 (DM1), USB10.A7 (D-), USB10.B7 (D-)
unnamed: U4.28 (DP1), USB10.A6 (D+), USB10.B6 (D+)
R0_A: ARD4.12 (PB7), D88.1 (K), D92.1 (K), D97.1 (K)
R0_L: ARD1.28 (PB4), D13.1 (K), D19.1 (K), D25.1 (K), D31.1 (K), D37.1 (K), D42.1 (K), D46.1 (K)
R0_N: ARD3.31 (PC6), D101.1 (K), D106.1 (K), D111.1 (K), D116.1 (K)
R0_R: ARD2.20 (PD2), D53.1 (K), D58.1 (K), D64.1 (K), D70.1 (K), D76.1 (K), D82.1 (K)
R1_A: ARD4.31 (PC6), D89.1 (K), D93.1 (K), D98.1 (K)
R1_L: ARD1.29 (PB5), D14.1 (K), D20.1 (K), D26.1 (K), D32.1 (K), D38.1 (K), D43.1 (K), D47.1 (K)
R1_N: ARD3.32 (PC7), D102.1 (K), D107.1 (K), D112.1 (K), D117.1 (K)
R1_R: ARD2.21 (PD3), D49.1 (K), D54.1 (K), D59.1 (K), D65.1 (K), D71.1 (K), D77.1 (K), D83.1 (K)
R2_A: ARD4.32 (PC7), D90.1 (K), D94.1 (K), D99.1 (K)
R2_L: ARD1.30 (PB6), D15.1 (K), D21.1 (K), D27.1 (K), D33.1 (K), D39.1 (K), D44.1 (K)
R2_N: ARD3.18 (PD0), D103.1 (K), D108.1 (K), D113.1 (K), D118.1 (K)
R2_R: ARD2.25 (PD4), D48.1 (K), D50.1 (K), D55.1 (K), D60.1 (K), D66.1 (K), D72.1 (K), D78.1 (K), D84.1 (K)
R3_A: ARD4.18 (PD0), D95.1 (K)
R3_L: ARD1.1 (PE6), D16.1 (K), D22.1 (K), D28.1 (K), D34.1 (K), D40.1 (K), D45.1 (K)
R3_N: ARD3.19 (PD1), D104.1 (K), D109.1 (K), D114.1 (K), D119.1 (K)
R3_R: ARD2.1 (PE6), D51.1 (K), D56.1 (K), D61.1 (K), D67.1 (K), D73.1 (K), D79.1 (K), D85.1 (K)
R4_A: ARD4.19 (PD1), D91.1 (K), D96.1 (K), D100.1 (K)
R4_L: ARD1.31 (PC6), D17.1 (K), D23.1 (K), D29.1 (K), D35.1 (K), D41.1 (K)
R4_N: ARD3.20 (PD2), D105.1 (K), D110.1 (K), D115.1 (K), D120.1 (K)
R4_R: ARD2.26 (PD6), D52.1 (K), D57.1 (K), D62.1 (K), D68.1 (K), D74.1 (K), D80.1 (K), D86.1 (K)
R5_L: ARD1.32 (PC7), D18.1 (K), D24.1 (K), D30.1 (K), D36.1 (K)
R5_N: ARD3.39 (PF4), D121.1 (K), D122.1 (K), D123.1 (K), D124.1 (K)
R5_R: ARD2.27 (PD7), D63.1 (K), D69.1 (K), D75.1 (K), D81.1 (K), D87.1 (K)
RGB_IN_A: ARD4.37 (PF6), RGB76.4 (DIN)
RGB_IN_L: ARD1.40 (PF1), RGB1.4 (DIN), USB3.A8 (SBU1), USB3.B8 (SBU2)
RGB_IN_N: ARD3.37 (PF6), RGB89.4 (DIN)
RGB_IN_R: ARD2.40 (PF1), RGB36.4 (DIN)
RGB_OUT_L: RGB35.2 (DOUT), USB4.A8 (SBU1), USB4.B8 (SBU2)
SW1: ARD4.41 (PF0), R1.1
SW2: ARD4.40 (PF1), R95.1
SW3: ARD4.39 (PF4), R10.1
SW4_1: D121.2 (A), RE6.S1
SW4_2: R88.2, RE6.S2, SW89.1, SW90.1, SW91.1, SW92.1, SW93.1
SW5_1: D122.2 (A), RE3.S1
SW5_2: R89.2, RE3.S2, SW94.1, SW95.1, SW96.1, SW97.1, SW98.1
SW6_1: D123.2 (A), RE7.S1
SW6_2: R90.2, RE7.S2, SW99.1, SW100.1, SW101.1, SW102.1, SW103.1
SW7_1: D124.2 (A), RE4.S1
SW7_2: R91.2, RE4.S2, SW104.1, SW105.1, SW106.1, SW107.1, SW108.1
VCC: D4.1 (K), D5.1 (K), D7.1 (K), D9.1 (K), D10.1 (K), D12.1 (K)

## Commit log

2021-03-12 Crea un nuevo archivo de texto
2021-05-09 Innitial commit
2021-05-09 Add correct references and footprints to components
2021-06-06 Add 3D keyboard layout
2021-06-06 Update PCB
    Added switch and LED layout
2021-06-06 Add USB ports
2021-06-07 added PCBs and plate
2021-07-04 Reorganizing files
2021-11-22 Switch to 75% layout
